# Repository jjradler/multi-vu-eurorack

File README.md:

# multi-vu-eurorack
Buffered multiple with an AVR-controlled VU meter and various available artistic panels.

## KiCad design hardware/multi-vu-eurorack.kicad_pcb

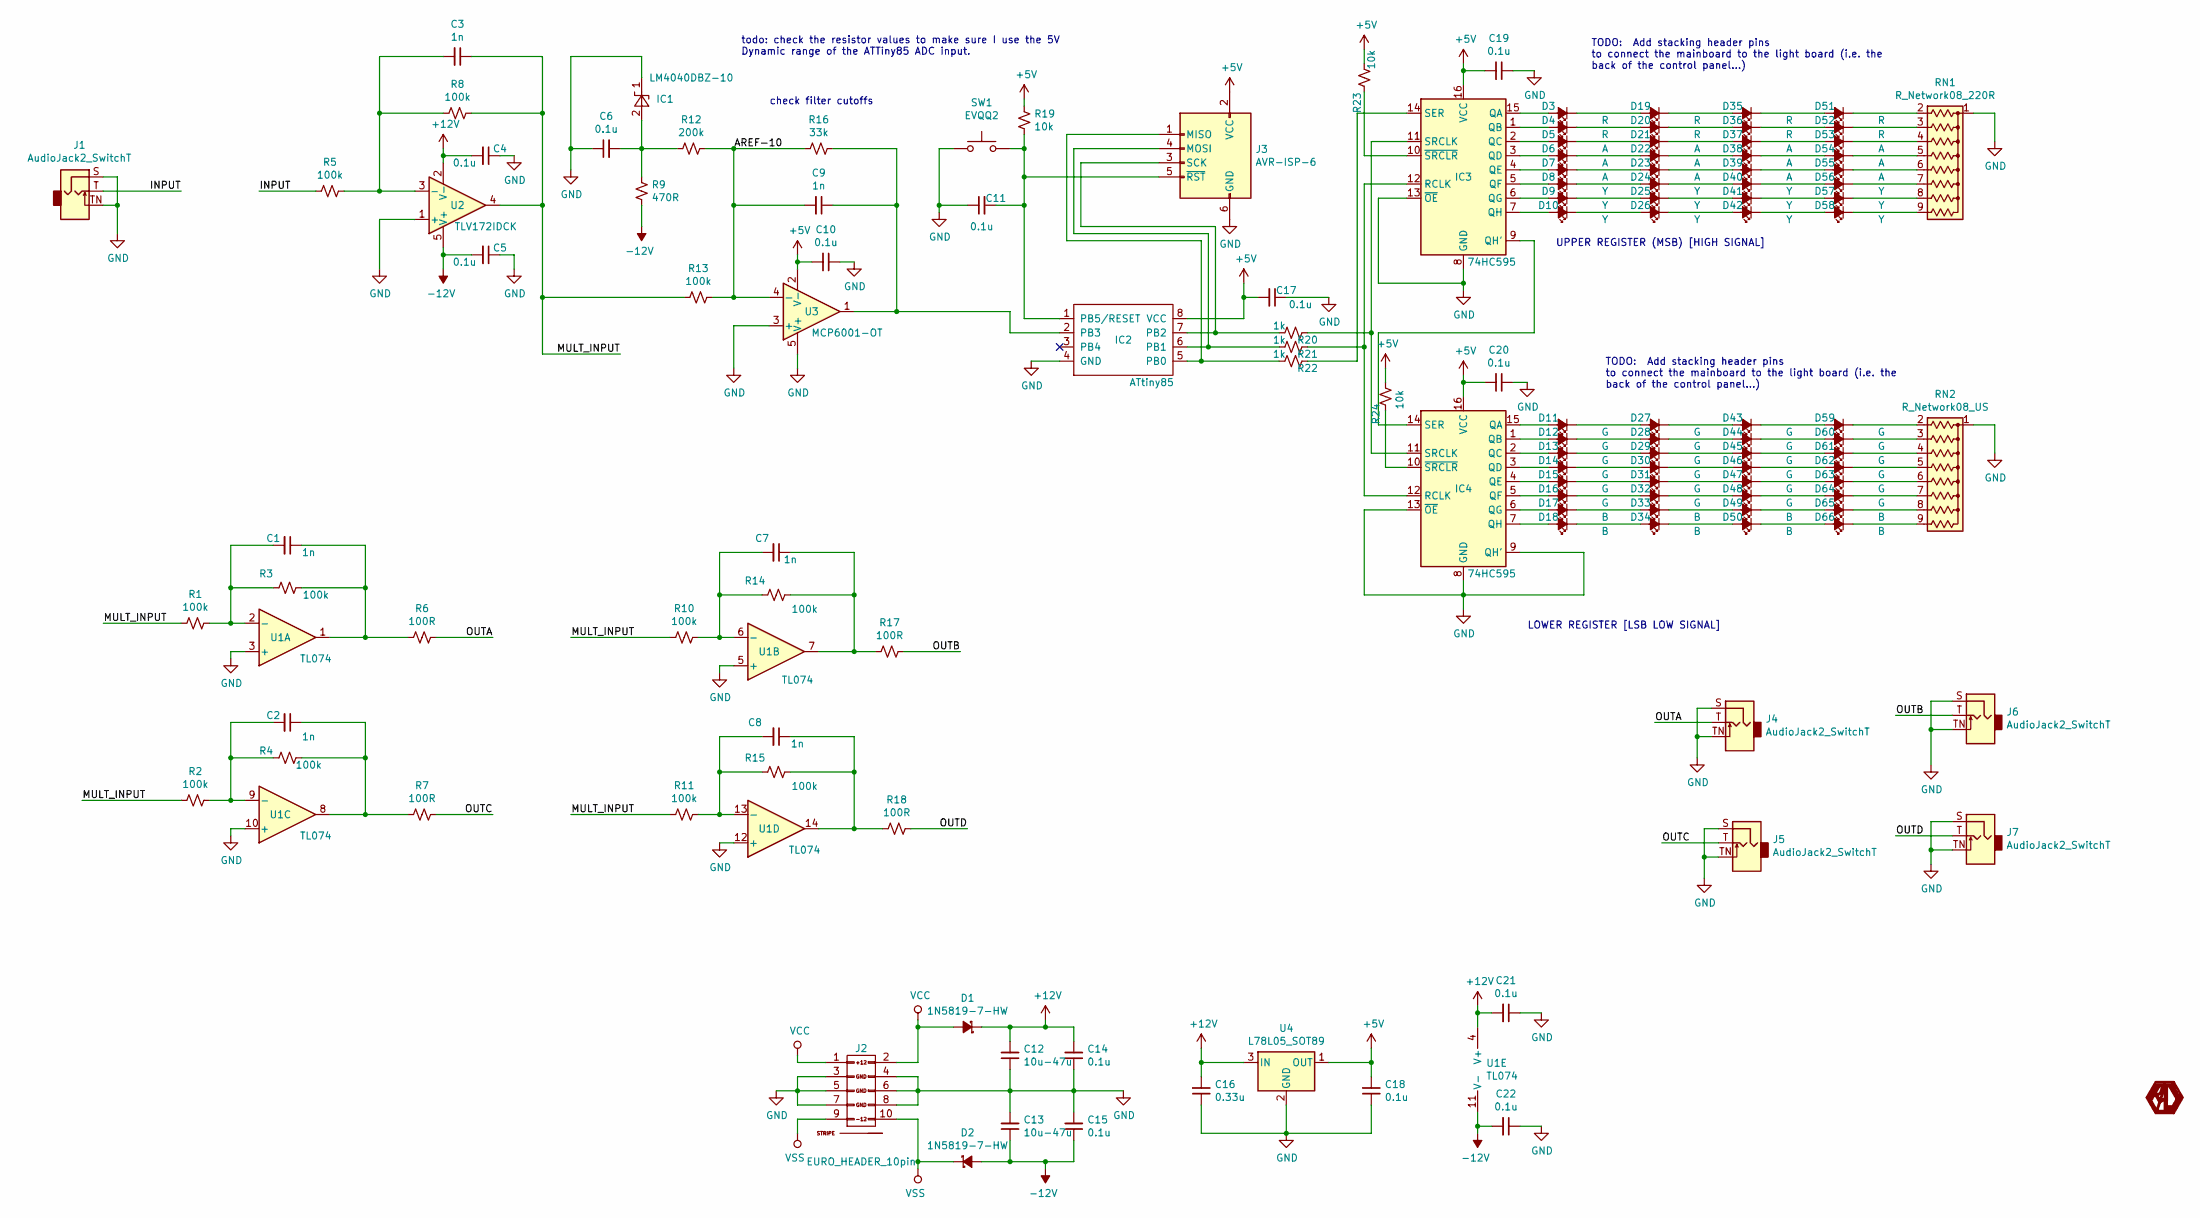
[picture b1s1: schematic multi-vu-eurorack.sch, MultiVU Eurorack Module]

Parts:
C1, C2, C3, C7, C8, C9: 1n; C_0603_1608Metric_Pad1.05x0.95mm_HandSolder
C4, C5, C6, C10, C11, C14, C15, C17, C18, C19, C20, C21, C22: 0.1u; C_0603_1608Metric_Pad1.05x0.95mm_HandSolder
C12, C13: 10u-47u; C_0603_1608Metric_Pad1.05x0.95mm_HandSolder
C16: 0.33u; C_0603_1608Metric_Pad1.05x0.95mm_HandSolder
D1, D2: 1N5819-7-HW; D_SOD-323_HandSoldering
D3, D4, D19, D20, D35, D36, D51, D52: R; LED_0603_1608Metric_Pad1.05x0.95mm_HandSolder
D5, D6, D7, D21, D22, D23, D37, D38, D39, D53, D54, D55: A; LED_0603_1608Metric_Pad1.05x0.95mm_HandSolder
D8, D9, D10, D24, D25, D26, D40, D41, D42, D56, D57, D58: Y; LED_0603_1608Metric_Pad1.05x0.95mm_HandSolder
D11, D12, D13, D14, D15, D16, D27, D28, D29, D30, D31, D32, D43, D44, D45, D46, D47, D48, D59, D60, D61, D62, D63, D64: G; LED_0603_1608Metric_Pad1.05x0.95mm_HandSolder
D17, D18, D33, D34, D49, D50, D65, D66: B; LED_0603_1608Metric_Pad1.05x0.95mm_HandSolder
IC1: LM4040DBZ-10; SOT-23
IC2: ATtiny85; SOIC-8_3.9x4.9mm_P1.27mm
IC3, IC4: 74HC595; TSSOP-16_4.4x5mm_P0.65mm
J1, J4, J5, J6, J7: AudioJack2_SwitchT; Jack_3.5mm_QingPu_WQP-PJ398SM_Vertical_CircularHoles
J2: EURO_HEADER_10pin; Header_2x05_Pitch2.54mm_TH_-12v_Label
J3: AVR-ISP-6; PinHeader_2x03_P2.54mm_Vertical
R1, R2, R3, R4, R5, R8, R10, R11, R13, R14, R15: 100k; C_0603_1608Metric_Pad1.05x0.95mm_HandSolder
R6, R7, R17, R18: 100R; C_0603_1608Metric_Pad1.05x0.95mm_HandSolder
R9: 470R; C_0603_1608Metric_Pad1.05x0.95mm_HandSolder
R12: 200k; C_0603_1608Metric_Pad1.05x0.95mm_HandSolder
R16: 33k; C_0603_1608Metric_Pad1.05x0.95mm_HandSolder
R19, R23, R24: 10k; C_0603_1608Metric_Pad1.05x0.95mm_HandSolder
R20, R21, R22: 1k; C_0603_1608Metric_Pad1.05x0.95mm_HandSolder
RN1: R_Network08_220R; RESCAXS64P320X160X60-10N
RN2: R_Network08_US; RESCAXS64P320X160X60-10N
SW1: EVQQ2; SW_SPST_EVQQ2
U1: TL074; TSSOP-14_4.4x5mm_P0.65mm
U2: TLV172IDCK; SOT-353_SC-70-5
U3: MCP6001-OT; SOT-23-5
U4: L78L05_SOT89; SOT-89-3

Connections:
+5V: C10.2, C17.2, C18.2, C19.2, C20.2, IC2.8 (VCC), IC3.16 (VCC), IC4.16 (VCC), J3.2 (VCC), R19.1, R23.2, R24.2, U3.2 (V-), U4.1 (OUT)
+12V: C4.2, C12.2, C14.2, C16.2, C21.2, D1.1 (K), U1.4 (V+), U2.2 (V-), U4.3 (IN)
-12V: C5.2, C13.1, C15.1, C22.2, D2.2 (A), R9.2, U1.11 (V-), U2.5 (V+)
/AREF-10: C9.2, R12.1, R13.1, R16.2, U3.4 (-)
/INPUT: J1.T, R5.2
/MULT_INPUT: C3.1, R1.2, R2.2, R8.1, R10.2, R11.2, R13.2, U2.4
/OUTA: J4.T, R6.1
/OUTB: J6.T, R17.1
/OUTC: J5.T, R7.1
/OUTD: J7.T, R18.1
GND: C4.1, C5.1, C6.1, C10.1, C11.1, C12.1, C13.2, C14.1, C15.2, C16.1, C17.1, C18.1, C19.1, C20.1, C21.1, C22.1, IC1.1 (K), IC2.4 (GND), IC3.8 (GND), IC3.13 (~OE), IC4.8 (GND), IC4.9 (QH'), IC4.13 (~OE), J1.S, J1.TN, J2.3 (GND), J2.4 (GND), J2.5 (GND), J2.6 (GND), J2.7 (GND), J2.8 (GND), J3.6 (GND), J4.S, J4.TN, J5.S, J5.TN, J6.S, J6.TN, J7.S, J7.TN, RN1.1 (common), RN2.1 (common), SW1.1, U1.3 (+), U1.5 (+), U1.10 (+), U1.12 (+), U2.1 (+), U3.3 (+), U3.5 (V+), U4.2 (GND)
unnamed: C1.1, R3.1, R6.2, U1.1
unnamed: C1.2, R1.1, R3.2, U1.2 (-)
unnamed: C2.1, R4.1, R7.2, U1.8
unnamed: C2.2, R2.1, R4.2, U1.9 (-)
unnamed: C3.2, R5.1, R8.2, U2.3 (-)
unnamed: C6.2, IC1.2 (A), R9.1, R12.2
unnamed: C7.1, R14.1, R17.2, U1.7
unnamed: C7.2, R10.1, R14.2, U1.6 (-)
unnamed: C8.1, R15.1, R18.2, U1.14
unnamed: C8.2, R11.1, R15.2, U1.13 (-)
unnamed: C9.1, IC2.2 (PB3), R16.1, U3.1
unnamed: C11.2, IC2.1 (PB5/RESET), J3.5 (~RST), R19.2, SW1.2
unnamed: D3.2 (A), IC3.15 (QA)
unnamed: D4.2 (A), IC3.1 (QB)
unnamed: D5.2 (A), IC3.2 (QC)
unnamed: D6.2 (A), IC3.3 (QD)
unnamed: D7.2 (A), IC3.4 (QE)
unnamed: D8.2 (A), IC3.5 (QF)
unnamed: D9.2 (A), IC3.6 (QG)
unnamed: D10.1 (K), D26.2 (A)
unnamed: D10.2 (A), IC3.7 (QH)
unnamed: D11.1 (K), D27.2 (A)
unnamed: D11.2 (A), IC4.15 (QA)
unnamed: D12.1 (K), D28.2 (A)
unnamed: D12.2 (A), IC4.1 (QB)
unnamed: D13.1 (K), D29.2 (A)
unnamed: D13.2 (A), IC4.2 (QC)
unnamed: D14.1 (K), D30.2 (A)
unnamed: D14.2 (A), IC4.3 (QD)
unnamed: D15.1 (K), D31.2 (A)
unnamed: D15.2 (A), IC4.4 (QE)
unnamed: D16.1 (K), D32.2 (A)
unnamed: D16.2 (A), IC4.5 (QF)
unnamed: D17.1 (K), D33.2 (A)
unnamed: D17.2 (A), IC4.6 (QG)
unnamed: D18.1 (K), D34.2 (A)
unnamed: D18.2 (A), IC4.7 (QH)
unnamed: D19.1 (K), D35.2 (A)
unnamed: D3.1 (K), D19.2 (A)
unnamed: D20.1 (K), D36.2 (A)
unnamed: D4.1 (K), D20.2 (A)
unnamed: D21.1 (K), D37.2 (A)
unnamed: D5.1 (K), D21.2 (A)
unnamed: D22.1 (K), D38.2 (A)
unnamed: D6.1 (K), D22.2 (A)
unnamed: D23.1 (K), D39.2 (A)
unnamed: D7.1 (K), D23.2 (A)
unnamed: D24.1 (K), D40.2 (A)
unnamed: D8.1 (K), D24.2 (A)
unnamed: D25.1 (K), D41.2 (A)
unnamed: D9.1 (K), D25.2 (A)
unnamed: D26.1 (K), D42.2 (A)
unnamed: D27.1 (K), D43.2 (A)
unnamed: D28.1 (K), D44.2 (A)
unnamed: D29.1 (K), D45.2 (A)
unnamed: D30.1 (K), D46.2 (A)
unnamed: D31.1 (K), D47.2 (A)
unnamed: D32.1 (K), D48.2 (A)
unnamed: D33.1 (K), D49.2 (A)
unnamed: D34.1 (K), D50.2 (A)
unnamed: D35.1 (K), D51.2 (A)
unnamed: D36.1 (K), D52.2 (A)
unnamed: D37.1 (K), D53.2 (A)
unnamed: D38.1 (K), D54.2 (A)
unnamed: D39.1 (K), D55.2 (A)
unnamed: D40.1 (K), D56.2 (A)
unnamed: D41.1 (K), D57.2 (A)
unnamed: D42.1 (K), D58.2 (A)
unnamed: D43.1 (K), D59.2 (A)
unnamed: D44.1 (K), D60.2 (A)
unnamed: D45.1 (K), D61.2 (A)
unnamed: D46.1 (K), D62.2 (A)
unnamed: D47.1 (K), D63.2 (A)
unnamed: D48.1 (K), D64.2 (A)
unnamed: D49.1 (K), D65.2 (A)
unnamed: D50.1 (K), D66.2 (A)
unnamed: D51.1 (K), RN1.2 (R1)
unnamed: D52.1 (K), RN1.3 (R2)
unnamed: D53.1 (K), RN1.4 (R3)
unnamed: D54.1 (K), RN1.5 (R4)
unnamed: D55.1 (K), RN1.6 (R5)
unnamed: D56.1 (K), RN1.7 (R6)
unnamed: D57.1 (K), RN1.8 (R7)
unnamed: D58.1 (K), RN1.9 (R8)
unnamed: D59.1 (K), RN2.2 (R1)
unnamed: D60.1 (K), RN2.3 (R2)
unnamed: D61.1 (K), RN2.4 (R3)
unnamed: D62.1 (K), RN2.5 (R4)
unnamed: D63.1 (K), RN2.6 (R5)
unnamed: D64.1 (K), RN2.7 (R6)
unnamed: D65.1 (K), RN2.8 (R7)
unnamed: D66.1 (K), RN2.9 (R8)
unnamed: IC2.5 (PB0), J3.1 (MISO), R22.2
unnamed: IC2.6 (PB1), J3.4 (MOSI), R21.2
unnamed: IC2.7 (PB2), J3.3 (SCK), R20.2
unnamed: IC3.9 (QH'), IC4.14 (SER)
unnamed: IC3.10 (~SRCLR), R23.1
unnamed: IC3.11 (SRCLK), IC4.11 (SRCLK), R20.1
unnamed: IC3.12 (RCLK), IC4.12 (RCLK), R21.1
unnamed: IC3.14 (SER), R22.1
unnamed: IC4.10 (~SRCLR), R24.1
VCC: D1.2 (A), J2.1 (+12V), J2.2 (+12V)
VSS: D2.1 (K), J2.9 (-12V), J2.10 (-12V)

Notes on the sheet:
todo: check the resistor values to make sure I use the 5V Dynamic range of the ATTiny85 ADC input.
UPPER REGISTER (MSB) [HIGH SIGNAL]
LOWER REGISTER [LSB LOW SIGNAL]
check filter cutoffs
TODO: Add stacking header pins to connect the mainboard to the light board (i.e. the back of the control panel…)

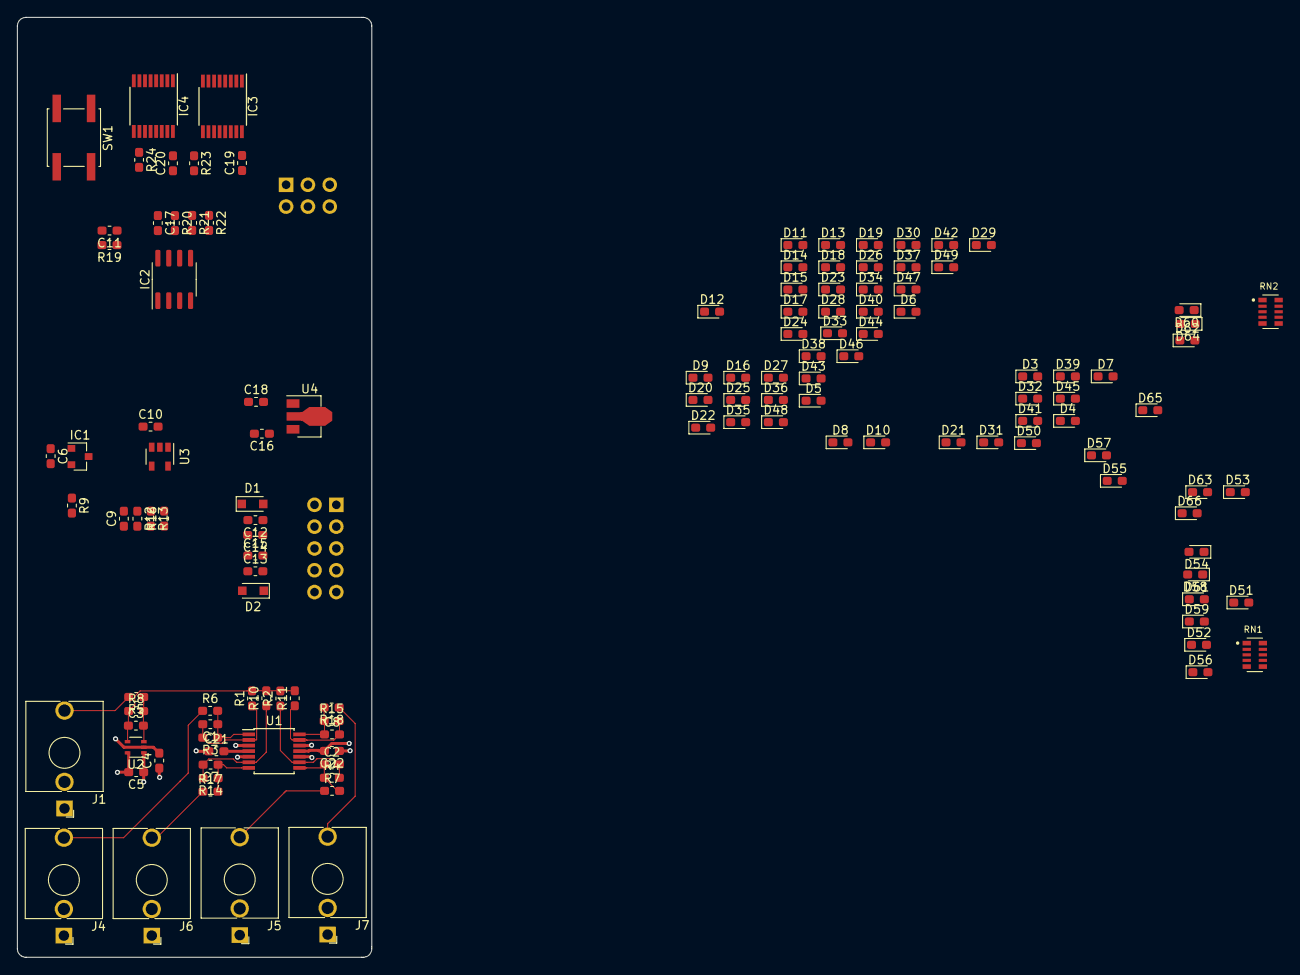
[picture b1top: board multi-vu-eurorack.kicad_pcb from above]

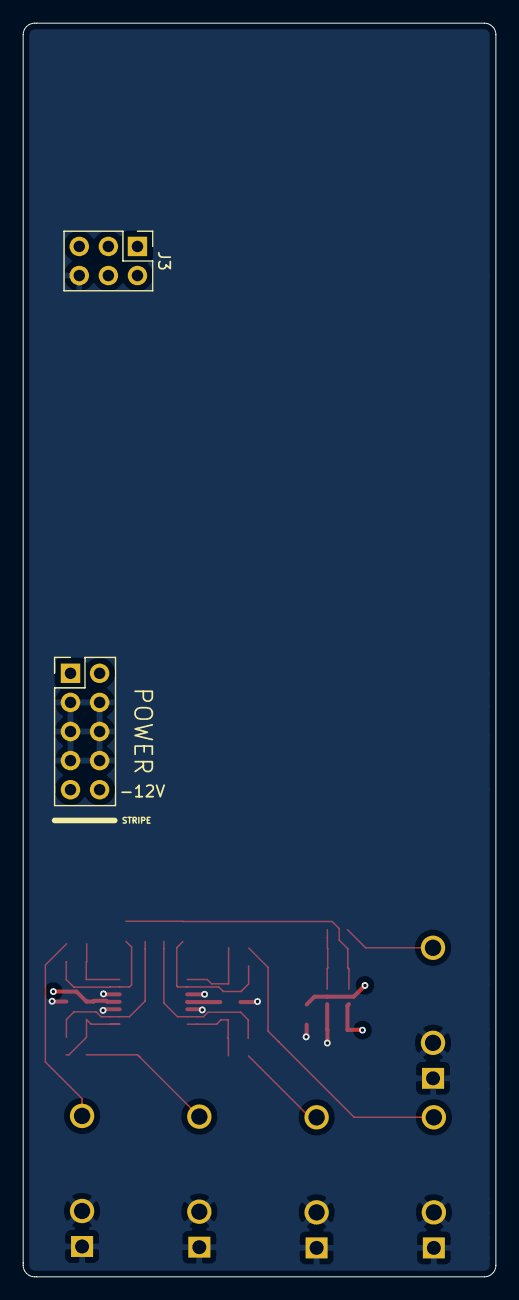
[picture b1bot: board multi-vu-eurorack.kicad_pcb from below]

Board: 2 copper layers, 41.3 x 109.5 mm, 130 parts (2 on the bottom side), 114 nets.

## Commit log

2021-04-11 Added to .gitignore list: C, C++, and Python ignores.
2021-04-11 Added values and annotations to the schematic. Added feedback loops and resistors to TL074 Mult Output amps. Added some notes to self.
2021-04-12 Added footprints to components in schematic. Started PCB layout and grouping subcircuits together in PCBNew.
2021-04-12 Added input and output jacks and a larger array of LEDs for the main panel.
2021-04-12 Updated netlist to include audio jacks. Corrected some small connection issues.
2021-04-13 Separated and arranged passives around mainboard ICs, started arranging LEDs on panel reverse.
2021-04-14 finalized the rough placements of the component subcircuit groups. Added traces between analog circuits for multiple subcircuit.
